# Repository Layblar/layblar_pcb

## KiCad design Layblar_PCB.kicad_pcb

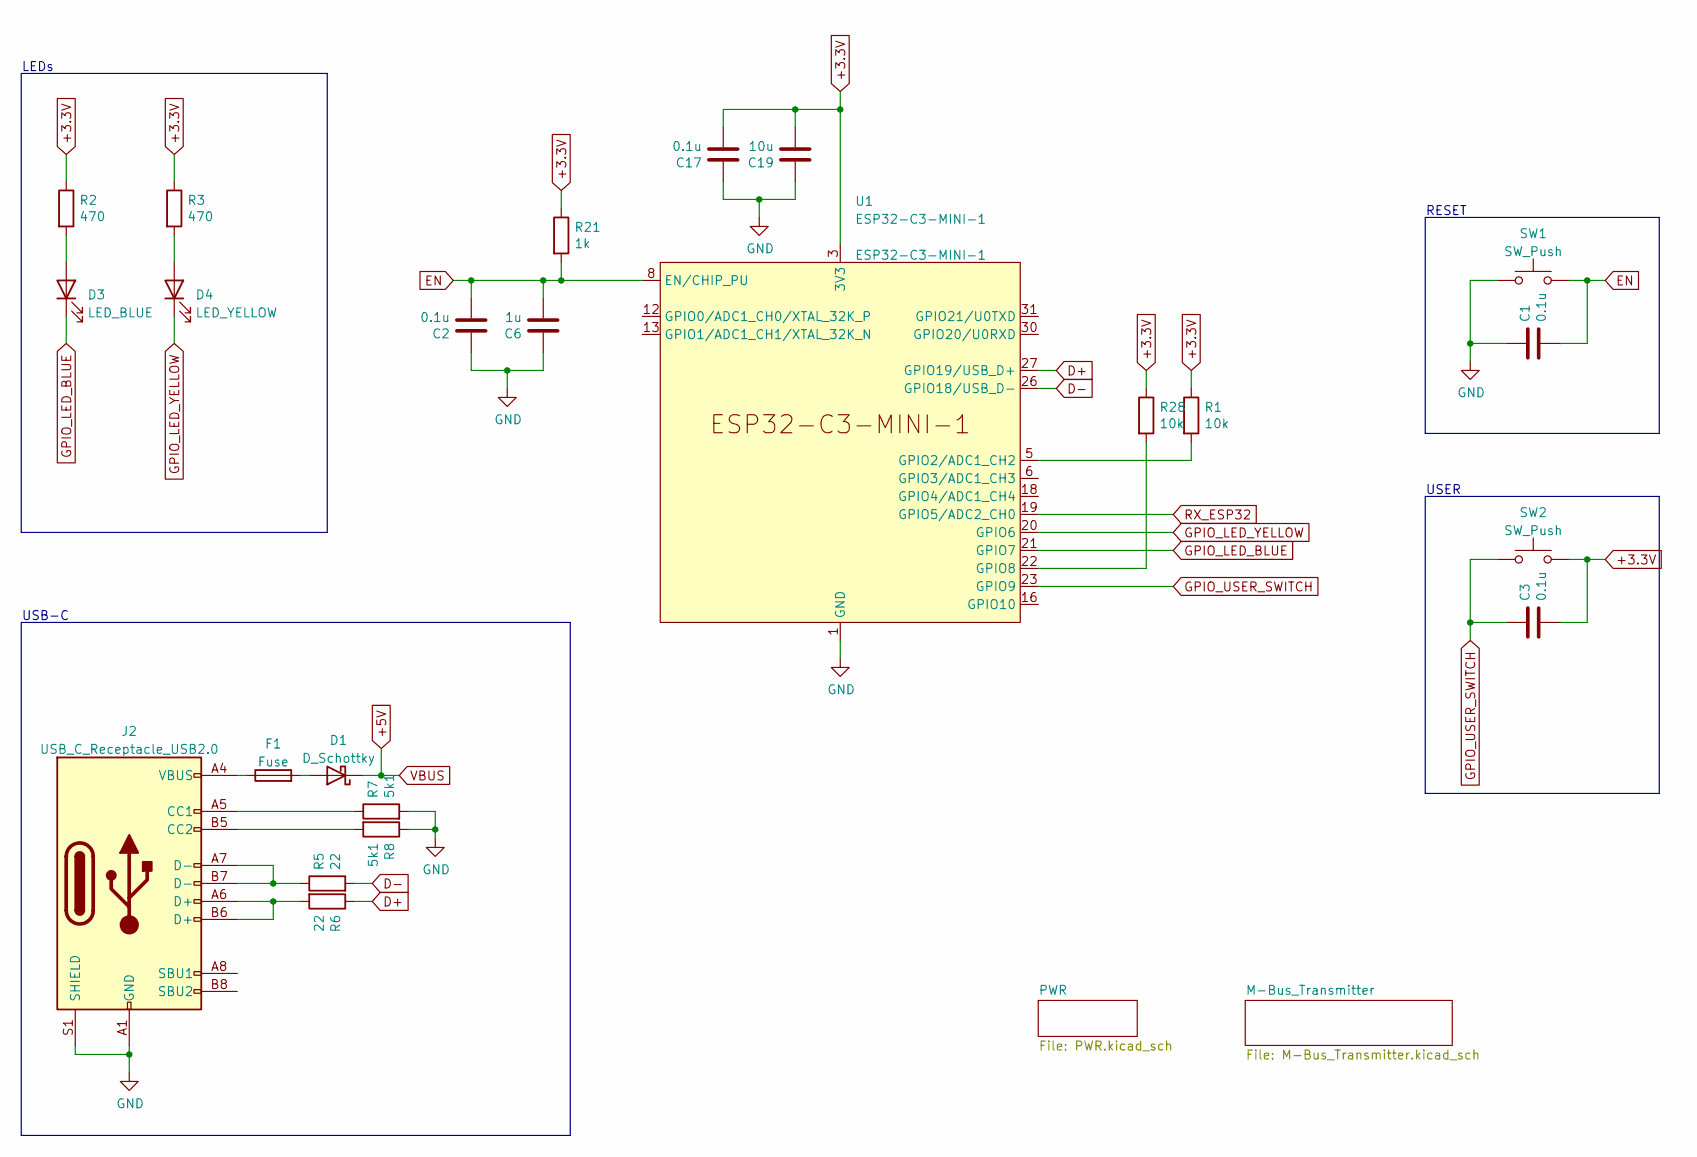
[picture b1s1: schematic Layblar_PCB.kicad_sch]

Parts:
C1, C2, C3, C17: 0.1u; C_0805_2012Metric
C6: 1u; C_0805_2012Metric
C19: 10u; C_0805_2012Metric
D1: D_Schottky; D_TUMD2
D3: LED_BLUE; LED_1206_3216Metric
D4: LED_YELLOW; LED_1206_3216Metric
F1: Fuse; Fuse_1812_4532Metric
J2: USB_C_Receptacle_USB2.0; USB_C_Receptacle_HRO_TYPE-C-31-M-12
R1, R28: 10k; R_0805_2012Metric
R2, R3: 470; R_0805_2012Metric
R5, R6: 22; R_0805_2012Metric
R7, R8: 5k1; R_0805_2012Metric
R21: 1k; R_0805_2012Metric
SW1, SW2: SW_Push; SW_Push_1P1T_NO_6x6mm_H9.5mm
U1: ESP32-C3-MINI-1

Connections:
+3.3V: C3.2, C17.2, C19.2, R1.1, R2.1, R3.1, R21.1, R28.1, SW2.2, U1.3 (3V3); also elsewhere on the board
+5V: D1.1 (K); also elsewhere on the board
D+: R6.1, U1.27 (GPIO19/USB_D+)
D-: R5.2, U1.26 (GPIO18/USB_D-)
EN: C1.2, C2.2, C6.2, R21.2, SW1.2, U1.8 (EN/CHIP_PU)
GND: C1.1, C2.1, C6.1, C17.1, C19.1, J2.A1 (GND), J2.A12 (GND), J2.B1 (GND), J2.B12 (GND), J2.S1 (SHIELD), R7.2, R8.1, SW1.1, U1.1 (GND), U1.2 (GND), U1.11 (GND), U1.14 (GND), U1.36 (GND), U1.37 (GND), U1.38 (GND), U1.39 (GND), U1.40 (GND), U1.41 (GND), U1.42 (GND), U1.43 (GND), U1.44 (GND), U1.45 (GND), U1.46 (GND), U1.47 (GND), U1.48 (GND), U1.49 (GND), U1.50 (GND), U1.51 (GND), U1.52 (GND), U1.53 (GND); also elsewhere on the board
GPIO_LED_BLUE: D3.1 (K), U1.21 (GPIO7)
GPIO_LED_YELLOW: D4.1 (K), U1.20 (GPIO6)
GPIO_USER_SWITCH: C3.1, SW2.1, U1.23 (GPIO9)
unnamed: D1.2 (A), F1.2
unnamed: D3.2 (A), R2.2
unnamed: D4.2 (A), R3.2
unnamed: F1.1, J2.A4 (VBUS), J2.A9 (VBUS), J2.B4 (VBUS), J2.B9 (VBUS)
unnamed: J2.A5 (CC1), R7.1
unnamed: J2.A6 (D+), J2.B6 (D+), R6.2
unnamed: J2.A7 (D-), J2.B7 (D-), R5.1
unnamed: J2.B5 (CC2), R8.2
unnamed: R1.2, U1.5 (GPIO2/ADC1_CH2)
unnamed: R28.2, U1.22 (GPIO8)
RX_ESP32: U1.19 (GPIO5/ADC2_CH0); also elsewhere on the board

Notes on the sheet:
USB-C
LEDs
USER
RESET

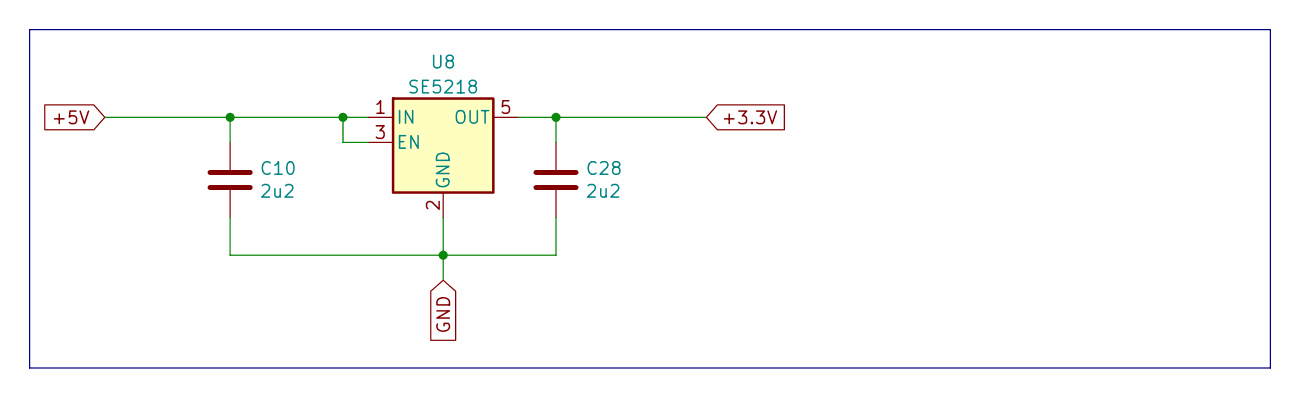
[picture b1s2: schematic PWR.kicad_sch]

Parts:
C10, C28: 2u2; C_0805_2012Metric
U8: SE5218; SOT-23-5

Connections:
+3.3V: C28.1, U8.5 (OUT); also elsewhere on the board
+5V: C10.1, U8.1 (IN), U8.3 (EN); also elsewhere on the board
GND: C10.2, C28.2, U8.2 (GND); also elsewhere on the board

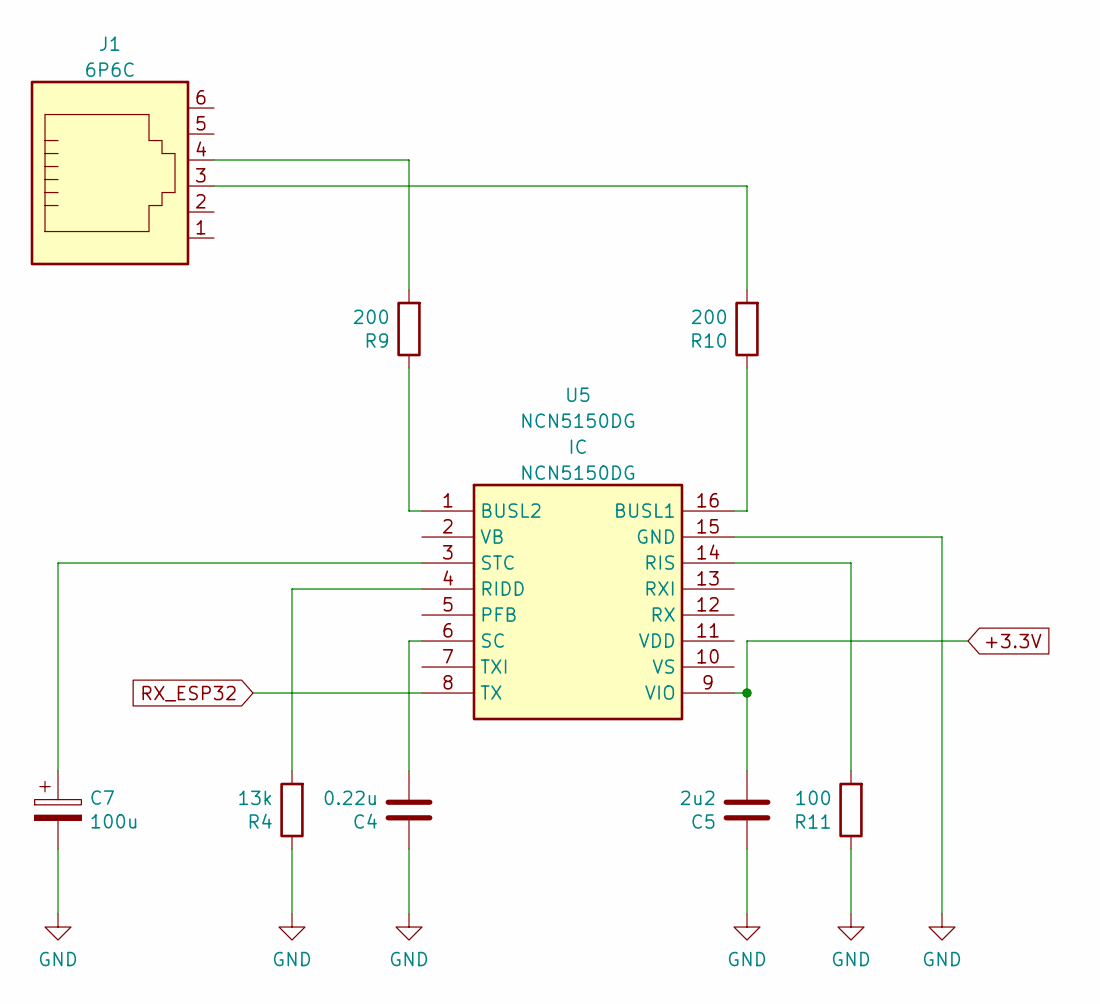
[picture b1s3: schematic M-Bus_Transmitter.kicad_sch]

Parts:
C4: 0.22u; C_0805_2012Metric
C5: 2u2; C_0805_2012Metric
C7: 100u; CP_Elec_6.3x7.7
J1: 6P6C; RJ12_Amphenol_54601
R4: 13k; R_0805_2012Metric
R9, R10: 200; R_0805_2012Metric
R11: 100; R_0805_2012Metric
U5: NCN5150DG; SOIC127P600X175-16N; Manufacturer_Part_Number NCN5150DG; Mouser Part Number 863-NCN5150DG

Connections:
+3.3V: C5.2, U5.9 (VIO); also elsewhere on the board
GND: C4.1, C5.1, C7.2, R4.1, R11.1, U5.15 (GND); also elsewhere on the board
unnamed: C4.2, U5.6 (SC)
unnamed: C7.1, U5.3 (STC)
unnamed: J1.3, R10.2
unnamed: J1.4, R9.2
unnamed: R4.2, U5.4 (RIDD)
unnamed: R9.1, U5.1 (BUSL2)
unnamed: R10.1, U5.16 (BUSL1)
unnamed: R11.2, U5.14 (RIS)
RX_ESP32: U5.8 (TX); also elsewhere on the board

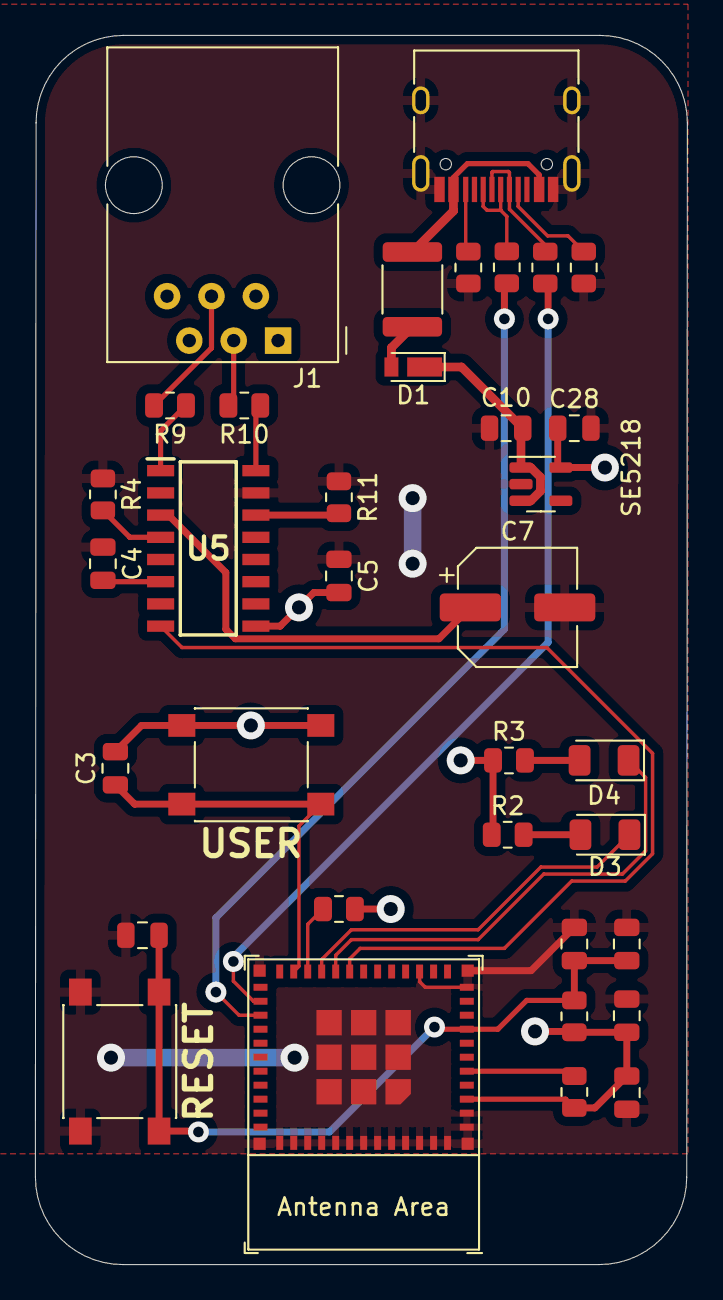
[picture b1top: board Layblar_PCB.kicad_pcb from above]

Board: 4 copper layers, 37.3 x 70.3 mm, 35 parts (0 on the bottom side), 28 nets.

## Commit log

2024-01-18 Created Version 1.0
    Refactored board with tipps after coaching
2024-01-24 Updated docs and fixed bug
2024-02-08 Updated R4 Value and docs
